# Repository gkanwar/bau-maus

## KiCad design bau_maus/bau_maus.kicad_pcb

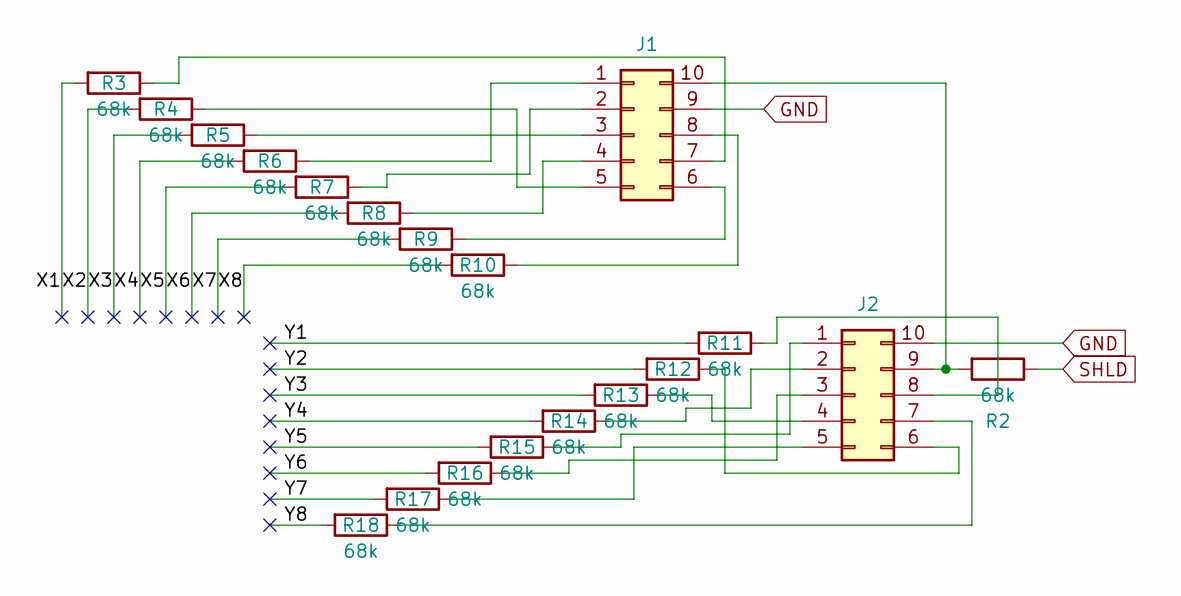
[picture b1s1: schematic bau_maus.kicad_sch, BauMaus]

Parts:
J1, J2: PinSocket_2x05_P1.27mm_Vertical_SMD
R2, R3, R4, R5, R6, R7, R8, R9, R10, R11, R12, R13, R14, R15, R16, R17, R18: 68k; R_0805_2012Metric_Pad1.20x1.40mm_HandSolder

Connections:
/X1: R3.2
/X2: R4.2
/X3: R5.2
/X4: R6.2
/X5: R7.2
/X6: R8.2
/X7: R9.2
/X8: R10.2
/Y1: R11.2
/Y2: R12.2
/Y3: R13.2
/Y4: R14.2
/Y5: R15.2
/Y6: R16.2
/Y7: R17.2
/Y8: R18.2
GND: J1.9, J2.10
unnamed: J1.1, R6.1
unnamed: J1.2, R7.1
unnamed: J1.3, R5.1
unnamed: J1.4, R8.1
unnamed: J1.5, R4.1
unnamed: J1.6, R9.1
unnamed: J1.7, R3.1
unnamed: J1.8, R10.1
unnamed: J1.10, J2.9, R2.2
unnamed: J2.1, R15.1
unnamed: J2.2, R14.1
unnamed: J2.3, R16.1
unnamed: J2.4, R13.1
unnamed: J2.5, R17.1
unnamed: J2.6, R12.1
unnamed: J2.7, R18.1
unnamed: J2.8, R11.1
SHLD: R2.1

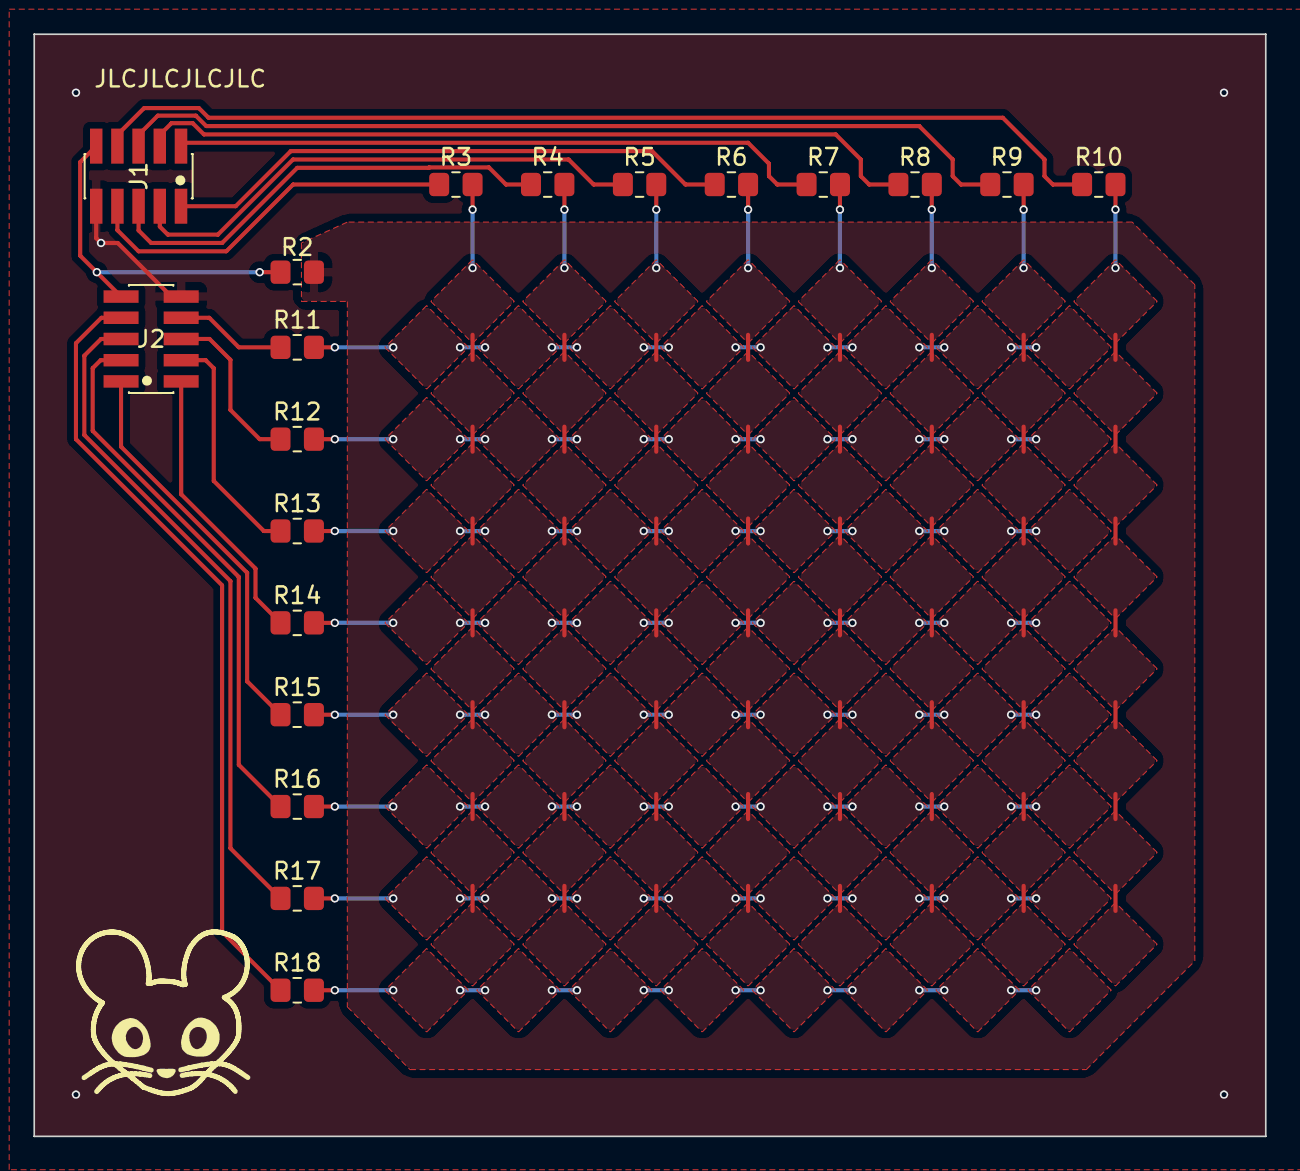
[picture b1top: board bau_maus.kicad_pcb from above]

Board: 2 copper layers, 73.8 x 66.0 mm, 19 parts (0 on the bottom side), 18 nets.

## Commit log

2023-12-25 Init repo with baumaus PCB
    Just adding this on to the unchat-42 order because its so damn cheap and
    shipping is expensive.
